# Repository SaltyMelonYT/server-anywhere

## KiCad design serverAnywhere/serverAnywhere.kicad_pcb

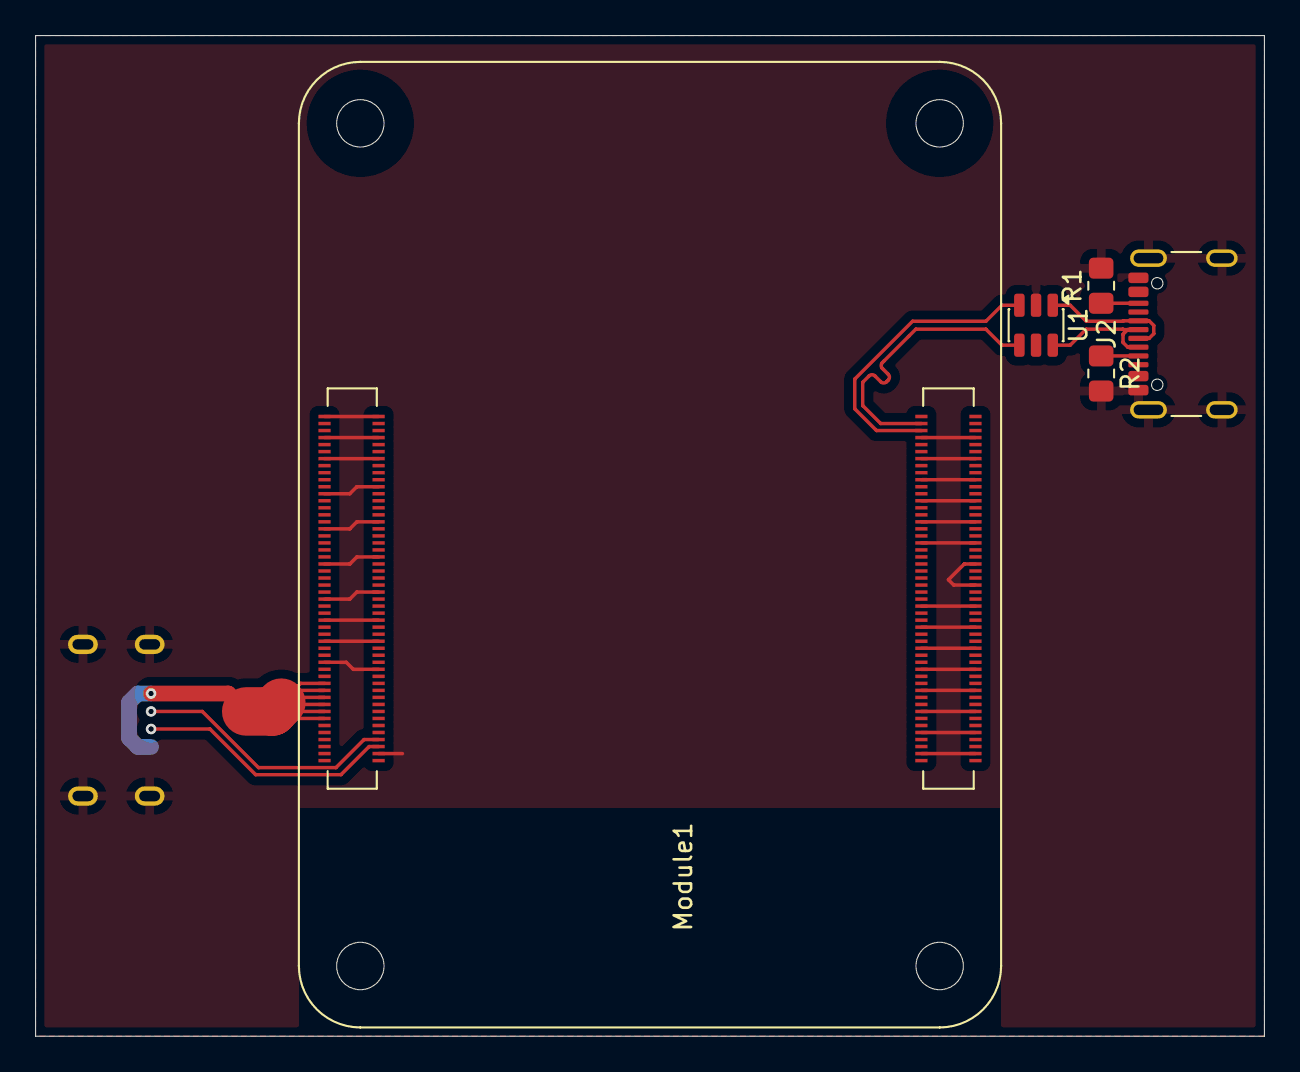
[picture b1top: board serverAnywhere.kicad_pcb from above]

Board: 2 copper layers, 70.0 x 57.0 mm, 6 parts (1 on the bottom side), 10 nets.

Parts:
J1: USB_C_Receptacle_PowerOnly_6P; USB_C_Receptacle_GCT_USB4125-xx-x-0190_6P_TopMnt_Horizontal
J2: USB_C_Receptacle_USB2.0_14P; USB_C_Receptacle_GCT_USB4105-xx-A_16P_TopMnt_Horizontal
Module1: ComputeModule5-CM5; Raspberry-Pi-5-Compute-Module
R1, R2: R_Small; R_0805_2012Metric_Pad1.20x1.40mm_HandSolder
U1: USBLC6-2SC6; SOT-23-6

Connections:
+5V: J1.A9 (VBUS), J1.B9 (VBUS), Module1.77 (+5v_(Input)), Module1.79 (+5v_(Input)), Module1.81 (+5v_(Input)), Module1.83 (+5v_(Input)), Module1.85 (+5v_(Input)), Module1.87 (+5v_(Input))
/CC1: J1.B5 (CC2), Module1.94 (CC1)
/CC2: J1.A5 (CC1), Module1.96 (CC2)
/HighSpeed/USB_N: Module1.103 (USB2_N), U1.4 (I/O2)
/HighSpeed/USB_P: Module1.105 (USB2_P), U1.3 (I/O2)
/USB_N: J2.A7 (D-), J2.B7 (D-), U1.6 (I/O1)
/USB_P: J2.A6 (D+), J2.B6 (D+), U1.1 (I/O1)
GND: J1.A12 (GND), J1.B12 (GND), J1.S1 (SHIELD), J2.A1 (GND), J2.A12 (GND), J2.B1 (GND), J2.B12 (GND), J2.S1 (SHIELD), Module1.1 (GND), Module1.2 (GND), Module1.7 (GND), Module1.8 (GND), Module1.13 (GND), Module1.14 (GND), Module1.22 (GND), Module1.23 (GND), Module1.32 (GND), Module1.33 (GND), Module1.42 (GND), Module1.43 (GND), Module1.52 (GND), Module1.53 (GND), Module1.59 (GND), Module1.60 (GND), Module1.65 (GND), Module1.66 (GND), Module1.71 (GND), Module1.74 (GND), Module1.98 (GND), Module1.107 (GND), Module1.108 (GND), Module1.113 (GND), Module1.114 (GND), Module1.119 (GND), Module1.120 (GND), Module1.125 (GND), Module1.126 (GND), Module1.131 (GND), Module1.132 (GND), Module1.137 (GND), Module1.138 (GND), Module1.144 (GND), Module1.150 (GND), Module1.155 (GND), Module1.156 (GND), Module1.161 (GND), Module1.162 (GND), Module1.167 (GND), Module1.168 (GND), Module1.173 (GND), Module1.174 (GND), Module1.179 (GND), Module1.180 (GND), Module1.185 (GND), Module1.186 (GND), Module1.191 (GND), Module1.192 (GND), Module1.197 (GND), Module1.198 (GND), R1.2, R2.2, U1.2 (GND)
unnamed: J2.A5 (CC1), R2.1
unnamed: J2.B5 (CC2), R1.1

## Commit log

2025-12-12 Begin
2025-12-12 Hopefully finished
